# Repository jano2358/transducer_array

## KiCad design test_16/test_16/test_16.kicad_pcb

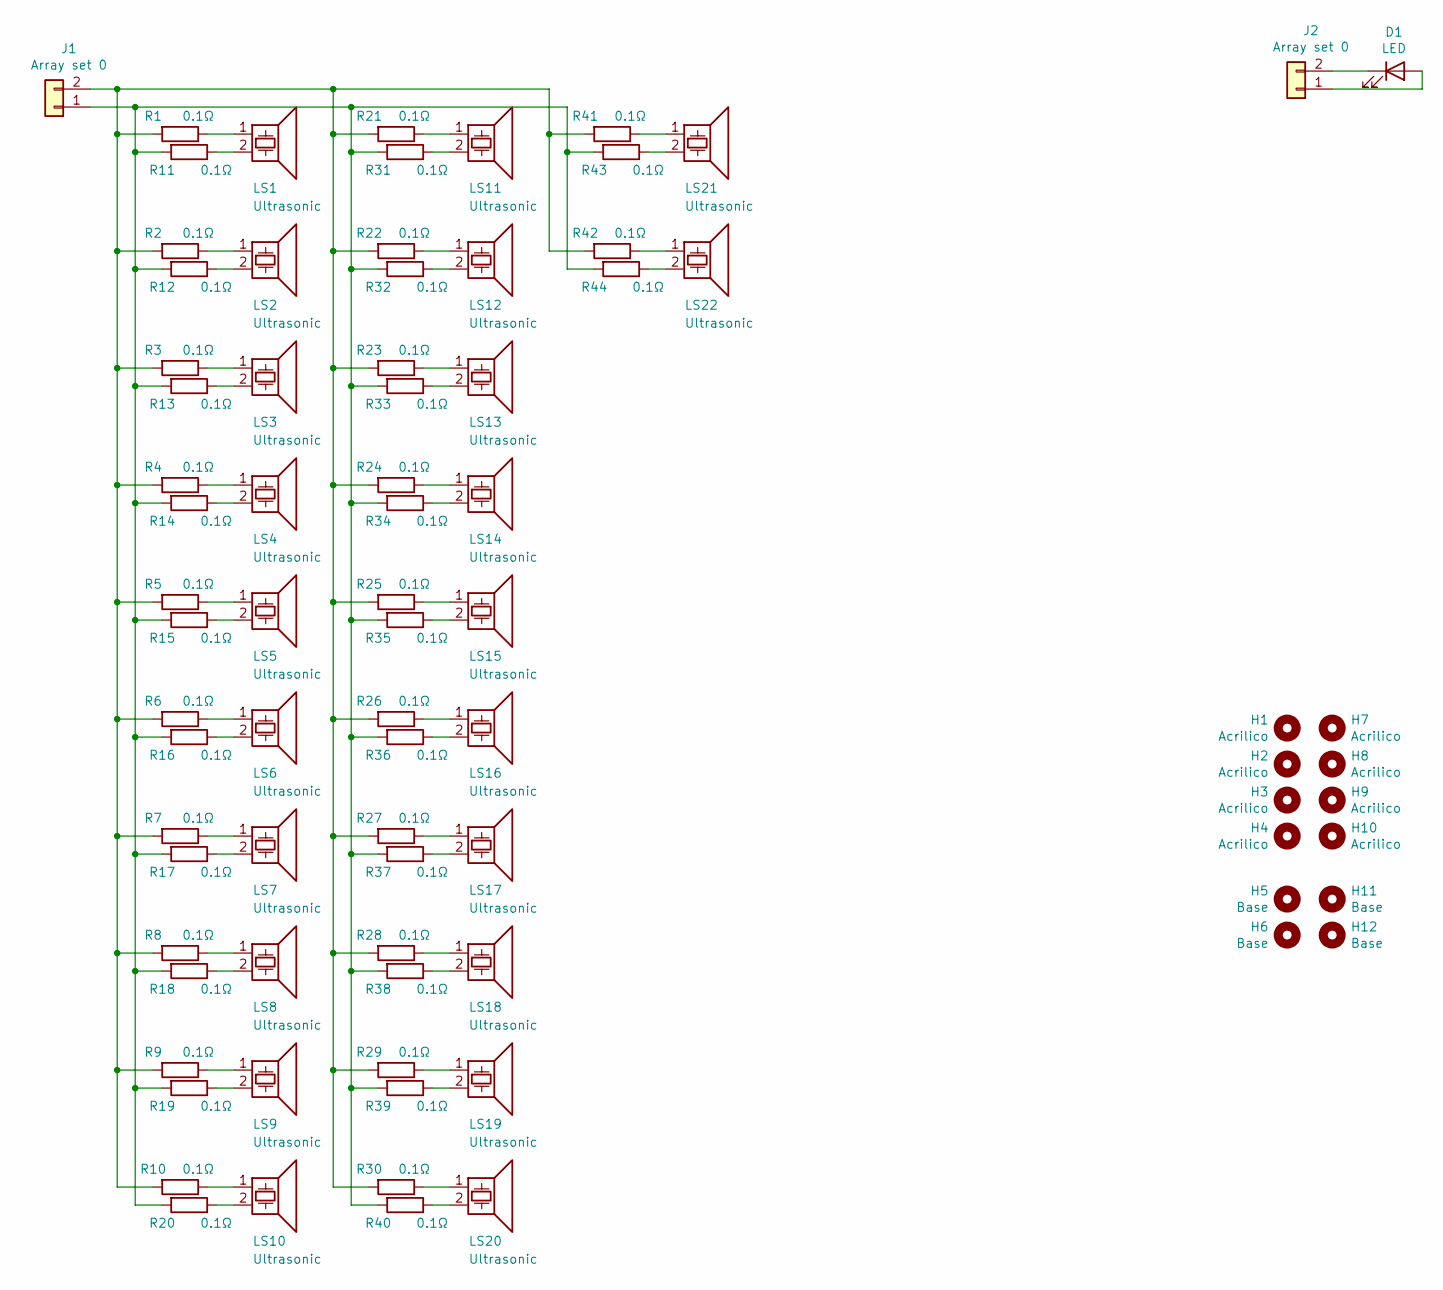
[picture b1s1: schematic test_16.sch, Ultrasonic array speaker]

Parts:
D1: LED; CREE_CXB1512
H1, H2, H3, H4, H7, H8, H9, H10: Acrilico; MountingHole_2.7mm
H5, H6, H11, H12: Base; MountingHole_2.7mm
J1, J2: Array set 0; PhoenixContact_MCV_1,5_2-G-3.5_1x02_P3.50mm_Vertical
LS1, LS2, LS3, LS4, LS5, LS6, LS7, LS8, LS9, LS10, LS11, LS12, LS13, LS14, LS15, LS16, LS17, LS18, LS19, LS20, LS21, LS22: Ultrasonic; Buzzer_MSO-A1640H12TR_D16__H12_P10
R1, R2, R3, R4, R5, R6, R7, R8, R9, R10, R11, R12, R13, R14, R15, R16, R17, R18, R19, R20, R21, R22, R23, R24, R25, R26, R27, R28, R29, R30, R31, R32, R33, R34, R35, R36, R37, R38, R39, R40, R41, R42, R43, R44: 0.1Ω; R_0603_1608Metric

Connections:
unnamed: D1.1 (K), J2.2
unnamed: D1.2 (A), J2.1
unnamed: J1.1, R11.2, R12.2, R13.2, R14.2, R15.2, R16.2, R17.2, R18.2, R19.2, R20.2, R31.2, R32.2, R33.2, R34.2, R35.2, R36.2, R37.2, R38.2, R39.2, R40.2, R43.2, R44.2
unnamed: J1.2, R1.2, R2.2, R3.2, R4.2, R5.2, R6.2, R7.2, R8.2, R9.2, R10.2, R21.2, R22.2, R23.2, R24.2, R25.2, R26.2, R27.2, R28.2, R29.2, R30.2, R41.2, R42.2
unnamed: LS1.1, R1.1
unnamed: LS1.2, R11.1
unnamed: LS2.1, R2.1
unnamed: LS2.2, R12.1
unnamed: LS3.1, R3.1
unnamed: LS3.2, R13.1
unnamed: LS4.1, R4.1
unnamed: LS4.2, R14.1
unnamed: LS5.1, R5.1
unnamed: LS5.2, R15.1
unnamed: LS6.1, R6.1
unnamed: LS6.2, R16.1
unnamed: LS7.1, R7.1
unnamed: LS7.2, R17.1
unnamed: LS8.1, R8.1
unnamed: LS8.2, R18.1
unnamed: LS9.1, R9.1
unnamed: LS9.2, R19.1
unnamed: LS10.1, R10.1
unnamed: LS10.2, R20.1
unnamed: LS11.1, R21.1
unnamed: LS11.2, R31.1
unnamed: LS12.1, R22.1
unnamed: LS12.2, R32.1
unnamed: LS13.1, R23.1
unnamed: LS13.2, R33.1
unnamed: LS14.1, R24.1
unnamed: LS14.2, R34.1
unnamed: LS15.1, R25.1
unnamed: LS15.2, R35.1
unnamed: LS16.1, R26.1
unnamed: LS16.2, R36.1
unnamed: LS17.1, R27.1
unnamed: LS17.2, R37.1
unnamed: LS18.1, R28.1
unnamed: LS18.2, R38.1
unnamed: LS19.1, R29.1
unnamed: LS19.2, R39.1
unnamed: LS20.1, R30.1
unnamed: LS20.2, R40.1
unnamed: LS21.1, R41.1
unnamed: LS21.2, R43.1
unnamed: LS22.1, R42.1
unnamed: LS22.2, R44.1

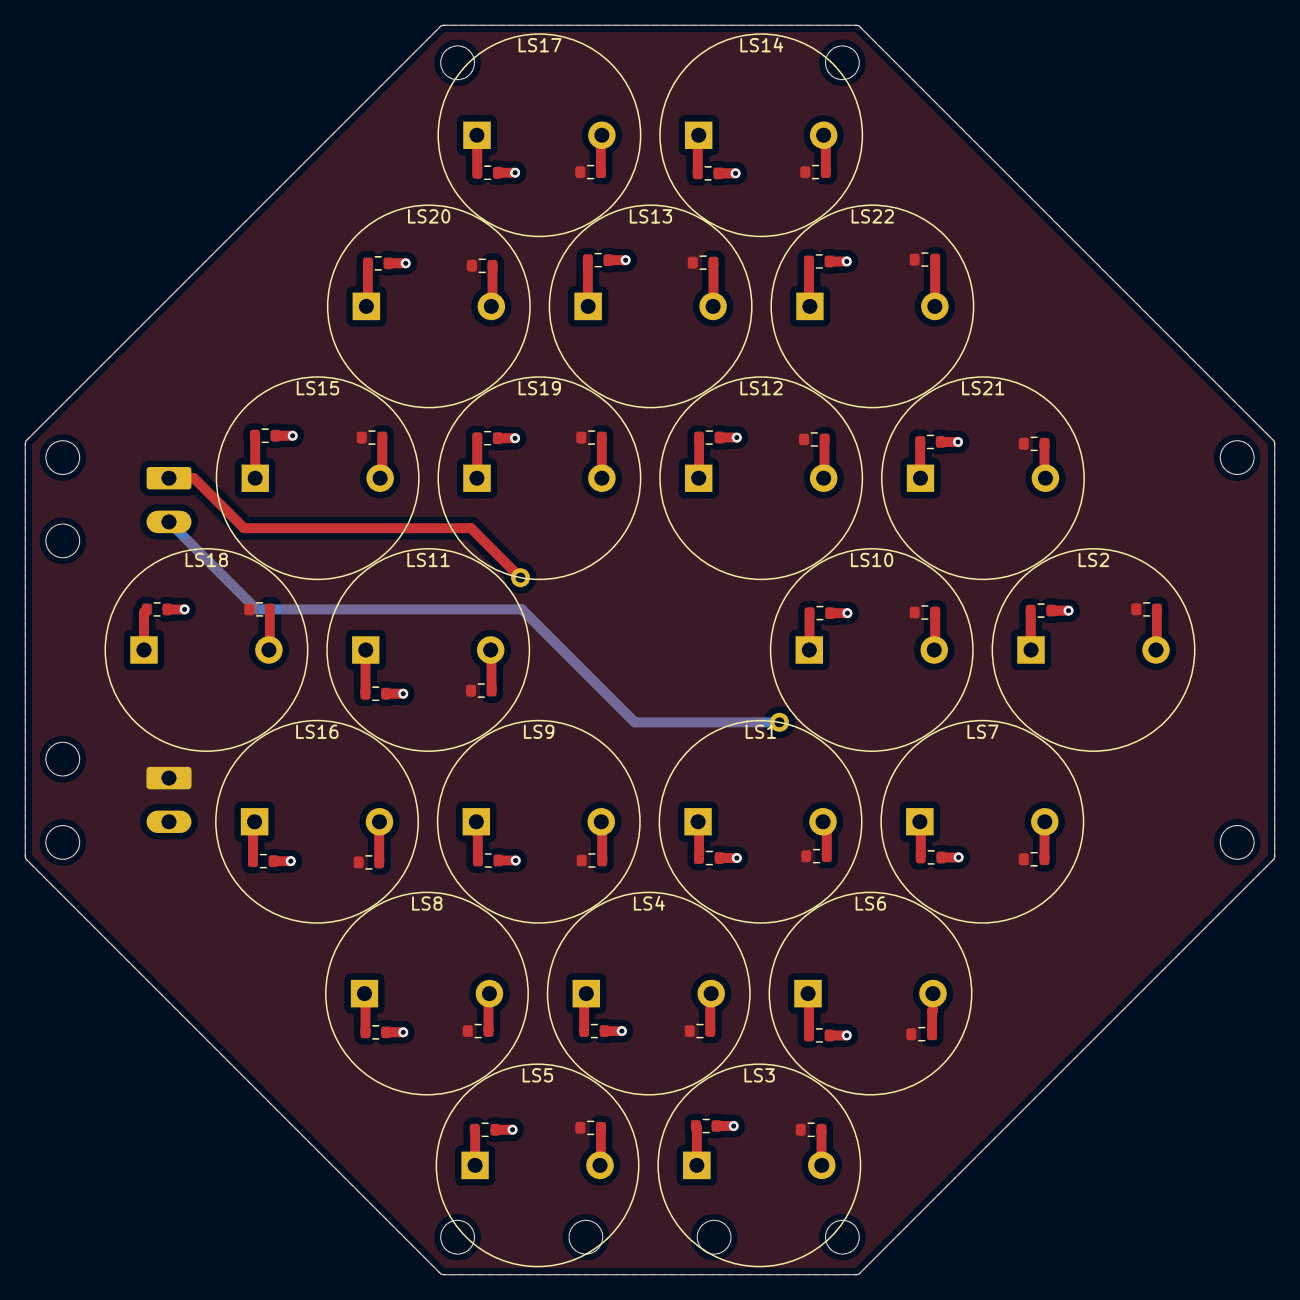
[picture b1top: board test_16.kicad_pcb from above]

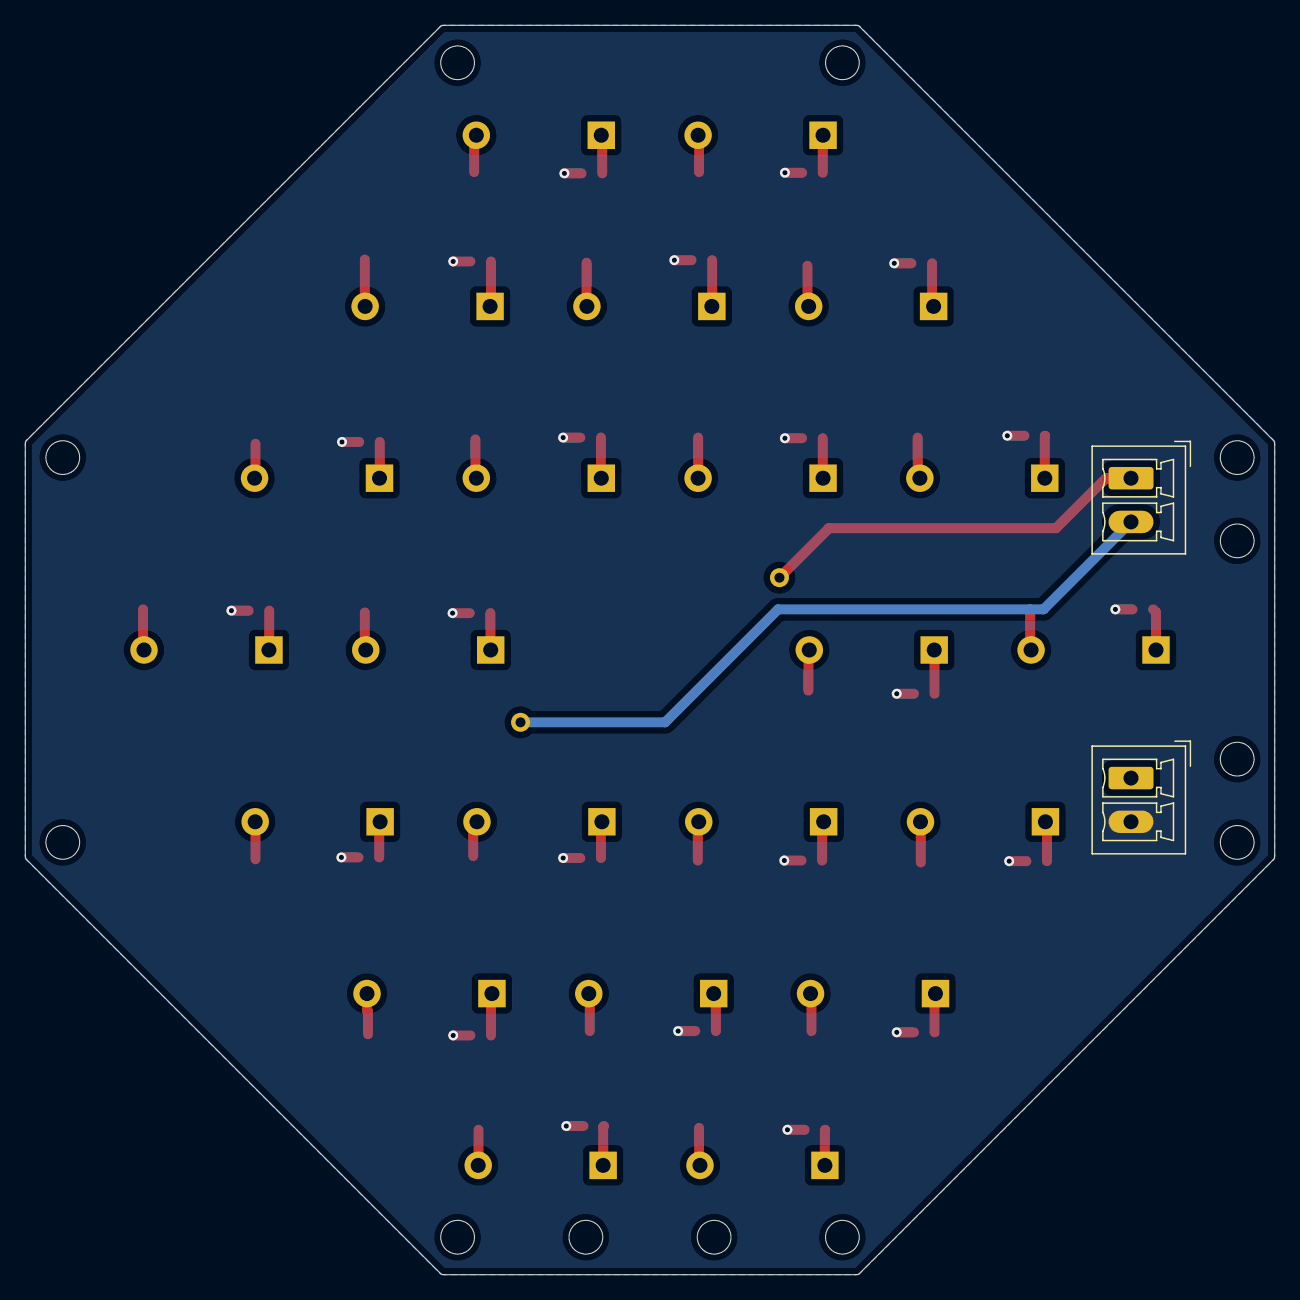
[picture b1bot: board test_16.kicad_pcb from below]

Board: 2 copper layers, 100.0 x 100.0 mm, 81 parts (2 on the bottom side), 48 nets.

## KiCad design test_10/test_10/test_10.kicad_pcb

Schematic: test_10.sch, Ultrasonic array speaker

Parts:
D1: LED; CREE_CXB1512
H1, H2, H3, H4, H7, H8, H9, H10: Acrilico; MountingHole_2.7mm
H5, H6, H11, H12: Base; MountingHole_2.7mm
J1, J2: Array set 0; PhoenixContact_MCV_1,5_2-G-3.5_1x02_P3.50mm_Vertical
LS1, LS2, LS3, LS4, LS5, LS6, LS7, LS8, LS9, LS10, LS11, LS12, LS13, LS14, LS15, LS16, LS17, LS18, LS19, LS20, LS21, LS22, LS23, LS24, LS25, LS26, LS27, LS28, LS29, LS30, LS31, LS32, LS33, LS34, LS35, LS36, LS37, LS38, LS39, LS40, LS41, LS42, LS43, LS44, LS45, LS46, LS47, LS48, LS49, LS50, LS51, LS52, LS53, LS54, LS55, LS56, LS57, LS58, LS59, LS60, LS61, LS62: Ultrasonic; Buzzer_MSO-A1040H07T_D10mm_H7mm
R1, R2, R3, R4, R5, R6, R7, R8, R9, R10, R11, R12, R13, R14, R15, R16, R17, R18, R19, R20, R21, R22, R23, R24, R25, R26, R27, R28, R29, R30, R31, R32, R33, R34, R35, R36, R37, R38, R39, R40, R41, R42, R43, R44, R45, R46, R47, R48, R49, R50, R51, R52, R53, R54, R55, R56, R57, R58, R59, R60, R61, R62, R63, R64, R65, R66, R67, R68, R69, R70, R71, R72, R73, R74, R75, R76, R77, R78, R79, R80, R81, R82, R83, R84, R85, R86, R87, R88, R89, R90, R91, R92, R93, R94, R95, R96, R97, R98, R99, R100, R101, R102, R103, R104, R105, R106, R107, R108, R109, R110, R111, R112, R113, R114, R115, R116, R117, R118, R119, R120, R121, R122, R123, R124: 0.1Ω; R_0603_1608Metric

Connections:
unnamed: D1.1, J2.1
unnamed: D1.2, J2.2
unnamed: J1.1, R11.2, R12.2, R13.2, R14.2, R15.2, R16.2, R17.2, R18.2, R19.2, R20.2, R31.2, R32.2, R33.2, R34.2, R35.2, R36.2, R37.2, R38.2, R39.2, R40.2, R51.2, R52.2, R53.2, R54.2, R55.2, R56.2, R57.2, R58.2, R59.2, R60.2, R71.2, R72.2, R73.2, R74.2, R75.2, R76.2, R77.2, R78.2, R79.2, R80.2, R91.2, R92.2, R93.2, R94.2, R95.2, R96.2, R97.2, R98.2, R99.2, R100.2, R110.2, R111.2, R112.2, R113.2, R114.2, R115.2, R116.2, R117.2, R118.2, R122.2, R123.2, R124.2
unnamed: J1.2, R1.2, R2.2, R3.2, R4.2, R5.2, R6.2, R7.2, R8.2, R9.2, R10.2, R21.2, R22.2, R23.2, R24.2, R25.2, R26.2, R27.2, R28.2, R29.2, R30.2, R41.2, R42.2, R43.2, R44.2, R45.2, R46.2, R47.2, R48.2, R49.2, R50.2, R61.2, R62.2, R63.2, R64.2, R65.2, R66.2, R67.2, R68.2, R69.2, R70.2, R81.2, R82.2, R83.2, R84.2, R85.2, R86.2, R87.2, R88.2, R89.2, R90.2, R101.2, R102.2, R103.2, R104.2, R105.2, R106.2, R107.2, R108.2, R109.2, R119.2, R120.2, R121.2
unnamed: LS1.1, R1.1
unnamed: LS1.2, R11.1
unnamed: LS2.1, R2.1
unnamed: LS2.2, R12.1
unnamed: LS3.1, R3.1
unnamed: LS3.2, R13.1
unnamed: LS4.1, R4.1
unnamed: LS4.2, R14.1
unnamed: LS5.1, R5.1
unnamed: LS5.2, R15.1
unnamed: LS6.1, R6.1
unnamed: LS6.2, R16.1
unnamed: LS7.1, R7.1
unnamed: LS7.2, R17.1
unnamed: LS8.1, R8.1
unnamed: LS8.2, R18.1
unnamed: LS9.1, R9.1
unnamed: LS9.2, R19.1
unnamed: LS10.1, R10.1
unnamed: LS10.2, R20.1
unnamed: LS11.1, R21.1
unnamed: LS11.2, R31.1
unnamed: LS12.1, R22.1
unnamed: LS12.2, R32.1
unnamed: LS13.1, R23.1
unnamed: LS13.2, R33.1
unnamed: LS14.1, R24.1
unnamed: LS14.2, R34.1
unnamed: LS15.1, R25.1
unnamed: LS15.2, R35.1
unnamed: LS16.1, R26.1
unnamed: LS16.2, R36.1
unnamed: LS17.1, R27.1
unnamed: LS17.2, R37.1
unnamed: LS18.1, R28.1
unnamed: LS18.2, R38.1
unnamed: LS19.1, R29.1
unnamed: LS19.2, R39.1
unnamed: LS20.1, R30.1
unnamed: LS20.2, R40.1
unnamed: LS21.1, R41.1
unnamed: LS21.2, R51.1
unnamed: LS22.1, R42.1
unnamed: LS22.2, R52.1
unnamed: LS23.1, R43.1
unnamed: LS23.2, R53.1
unnamed: LS24.1, R44.1
unnamed: LS24.2, R54.1
unnamed: LS25.1, R45.1
unnamed: LS25.2, R55.1
unnamed: LS26.1, R46.1
unnamed: LS26.2, R56.1
unnamed: LS27.1, R47.1
unnamed: LS27.2, R57.1
unnamed: LS28.1, R48.1
unnamed: LS28.2, R58.1
unnamed: LS29.1, R49.1
unnamed: LS29.2, R59.1
unnamed: LS30.1, R50.1
unnamed: LS30.2, R60.1
unnamed: LS31.1, R61.1
unnamed: LS31.2, R71.1
unnamed: LS32.1, R62.1
unnamed: LS32.2, R72.1
unnamed: LS33.1, R63.1
unnamed: LS33.2, R73.1
unnamed: LS34.1, R64.1
unnamed: LS34.2, R74.1
unnamed: LS35.1, R65.1
unnamed: LS35.2, R75.1
unnamed: LS36.1, R66.1
unnamed: LS36.2, R76.1
unnamed: LS37.1, R67.1
unnamed: LS37.2, R77.1
unnamed: LS38.1, R68.1
unnamed: LS38.2, R78.1
unnamed: LS39.1, R69.1
unnamed: LS39.2, R79.1
unnamed: LS40.1, R70.1
unnamed: LS40.2, R80.1
unnamed: LS41.1, R81.1
unnamed: LS41.2, R91.1
unnamed: LS42.1, R82.1
unnamed: LS42.2, R92.1
unnamed: LS43.1, R83.1
unnamed: LS43.2, R93.1
unnamed: LS44.1, R84.1
unnamed: LS44.2, R94.1
unnamed: LS45.1, R85.1
unnamed: LS45.2, R95.1
unnamed: LS46.1, R86.1
unnamed: LS46.2, R96.1
unnamed: LS47.1, R87.1
unnamed: LS47.2, R97.1
unnamed: LS48.1, R88.1
unnamed: LS48.2, R98.1
unnamed: LS49.1, R89.1
unnamed: LS49.2, R99.1
unnamed: LS50.1, R90.1
unnamed: LS50.2, R100.1
unnamed: LS51.1, R101.1
unnamed: LS51.2, R110.1
unnamed: LS52.1, R102.1
unnamed: LS52.2, R111.1
unnamed: LS53.1, R103.1
unnamed: LS53.2, R112.1
unnamed: LS54.1, R104.1
unnamed: LS54.2, R113.1
unnamed: LS55.1, R105.1
unnamed: LS55.2, R114.1
unnamed: LS56.1, R106.1
unnamed: LS56.2, R115.1
unnamed: LS57.1, R107.1
unnamed: LS57.2, R116.1
unnamed: LS58.1, R108.1
unnamed: LS58.2, R117.1
unnamed: LS59.1, R109.1
unnamed: LS59.2, R118.1
unnamed: LS60.1, R119.1
unnamed: LS60.2, R122.1
unnamed: LS61.1, R120.1
unnamed: LS61.2, R123.1
unnamed: LS62.1, R121.1
unnamed: LS62.2, R124.1

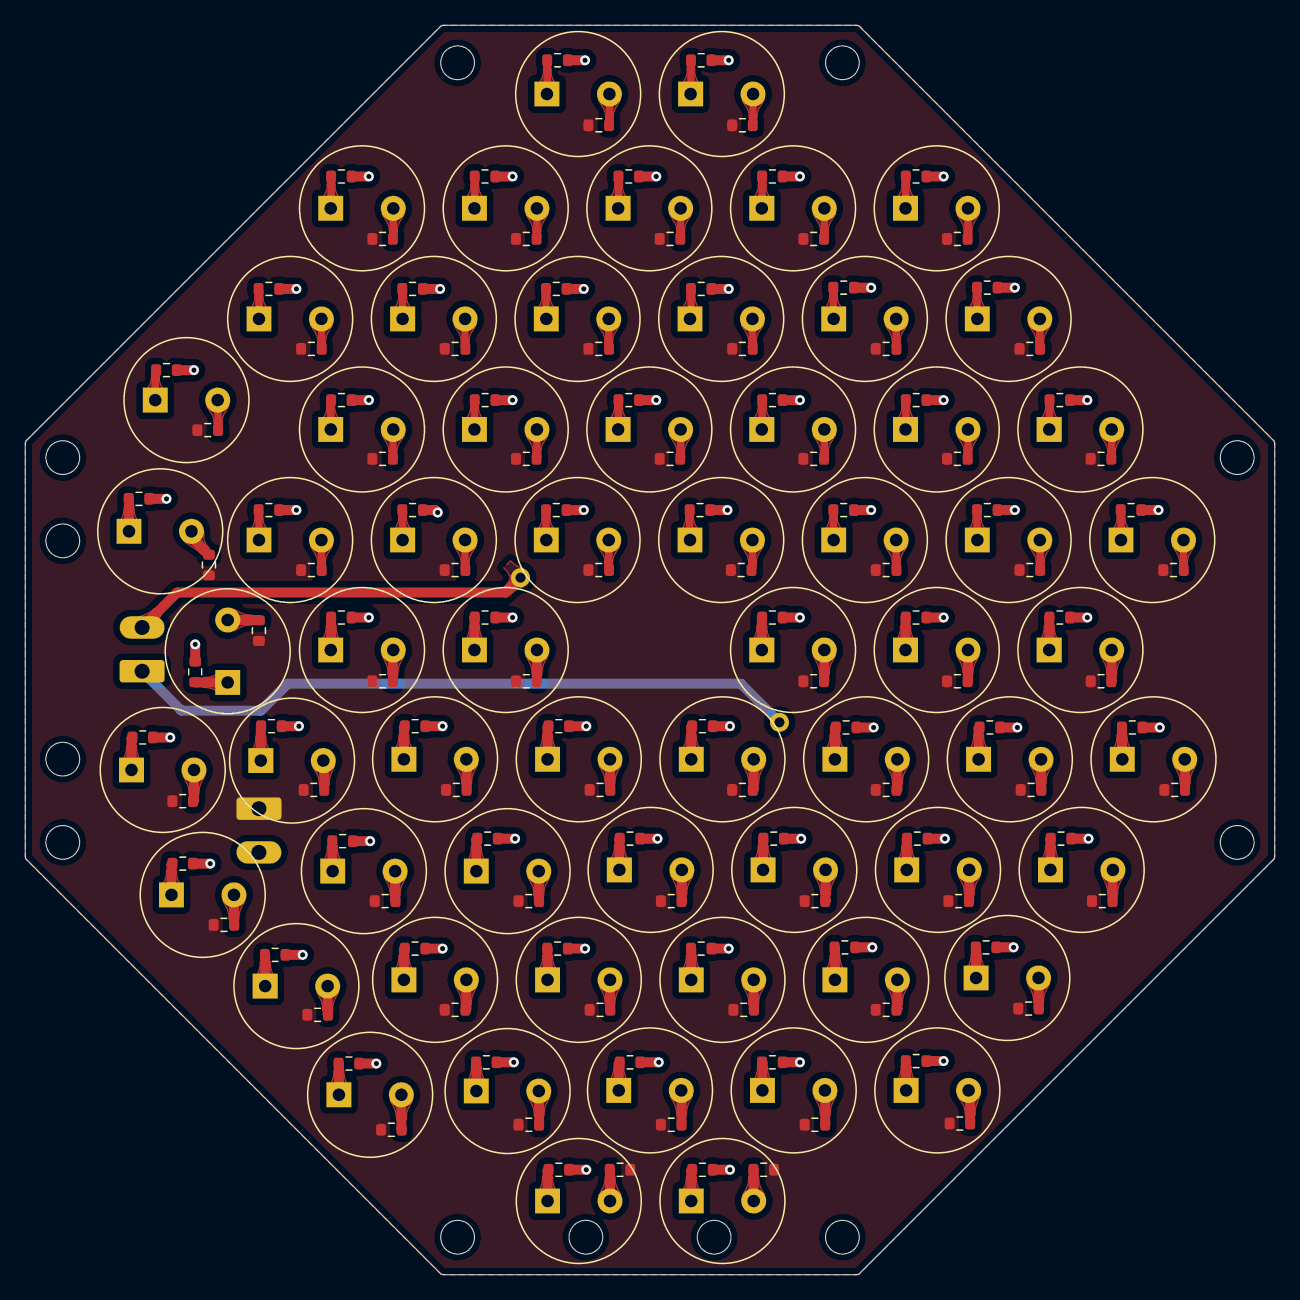
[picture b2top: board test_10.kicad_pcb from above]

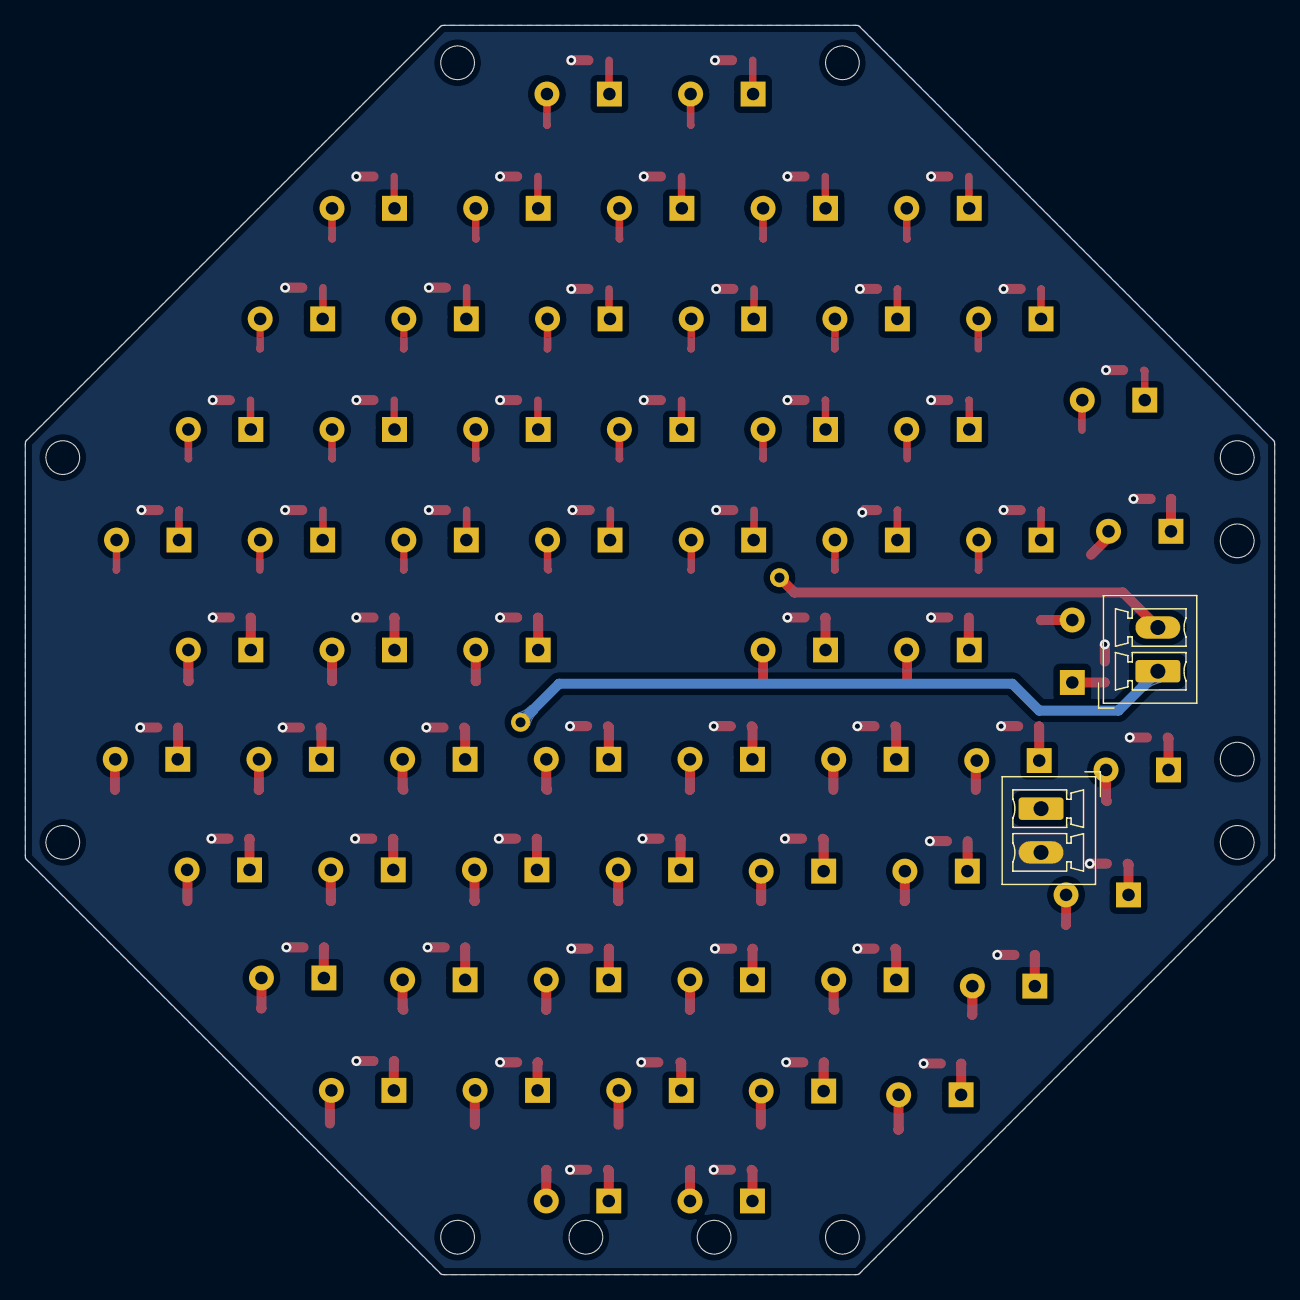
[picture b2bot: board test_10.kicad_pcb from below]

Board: 2 copper layers, 100.0 x 100.0 mm, 201 parts (2 on the bottom side), 128 nets.

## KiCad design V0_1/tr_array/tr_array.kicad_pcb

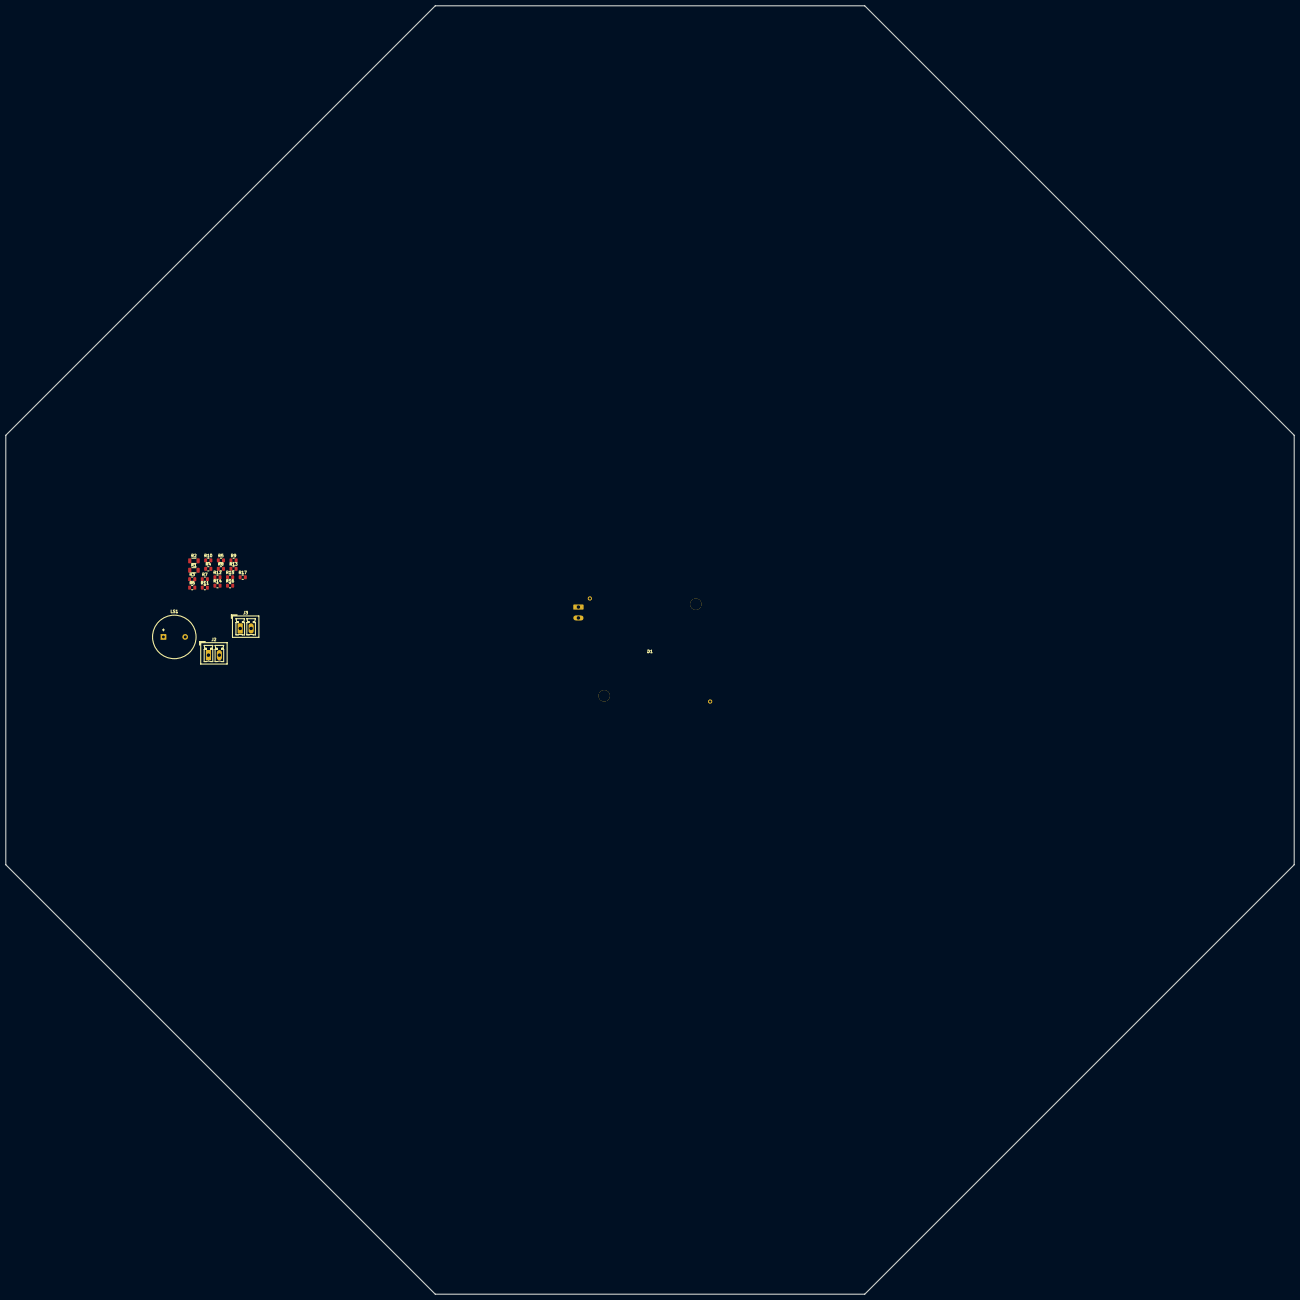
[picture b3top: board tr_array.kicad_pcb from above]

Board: 2 copper layers, 450.0 x 450.0 mm, 22 parts (1 on the bottom side), 7 nets, no tracks yet.

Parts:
D1: LED; CXM-32_LED_38x38mm
J1: LED; PhoenixContact_MCV_1,5_2-G-3.81_1x02_P3.81mm_Vertical
J2: Array set 0; PhoenixContact_MCV_1,5_2-G-3.81_1x02_P3.81mm_Vertical
J3: Array set 1; PhoenixContact_MCV_1,5_2-G-3.81_1x02_P3.81mm_Vertical
LS1: Ultrasonic; Buzzer_15x7.5RM7.6
R1, R2: 0Ω; R_1206_3216Metric
R3, R4, R5, R6, R7, R8, R9, R10, R11, R12, R13, R14, R15, R16, R17: 0.1Ω; R_0805_2012Metric

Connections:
unnamed: D1.1, J1.2
unnamed: D1.2, J1.1
unnamed: J2.1, R2.1
unnamed: J2.2, R1.1, R3.2, R4.2, R5.2, R6.2, R7.2, R8.2, R9.2, R10.2, R11.2, R12.2
unnamed: J3.1, R2.2
unnamed: J3.2, R1.2, R13.2, R14.2, R15.2, R16.2, R17.2
unnamed: LS1.1, R3.1

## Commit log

2021-06-14 first commit #
2021-06-14 renumber
2021-06-20 pcb finish
2021-06-23 3 trans mas
2021-06-29 bracket alignement
2021-07-04 gerbers ready
